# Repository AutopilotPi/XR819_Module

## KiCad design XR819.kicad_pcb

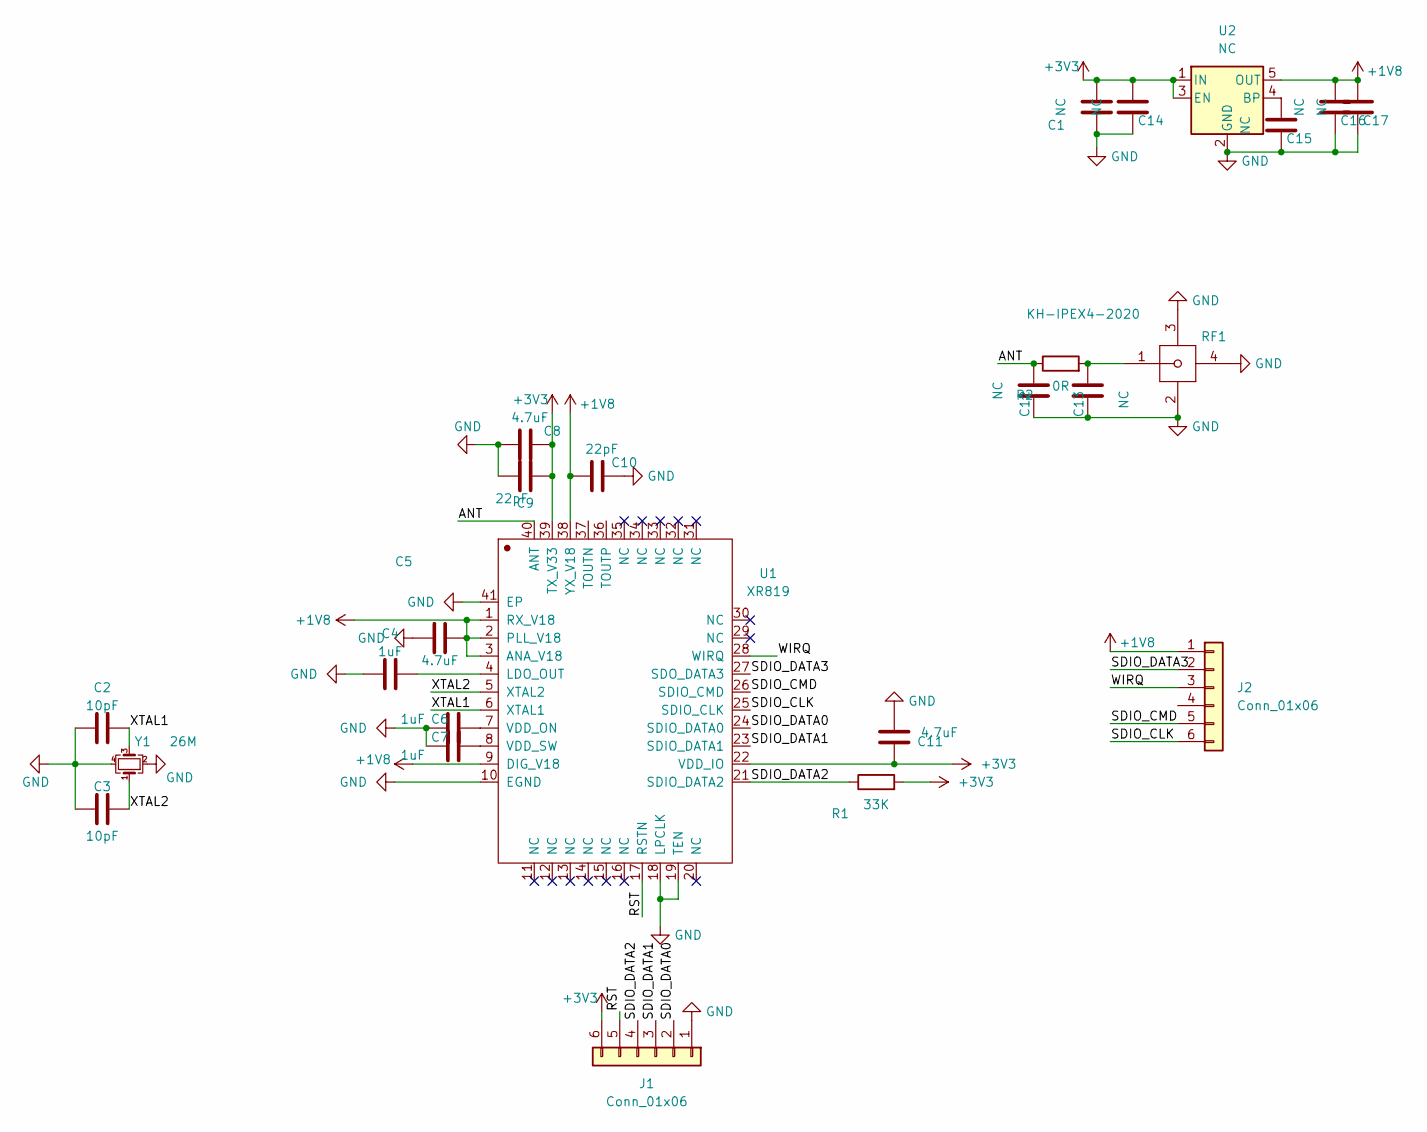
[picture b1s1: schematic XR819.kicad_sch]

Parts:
C1, C12, C13, C14, C15, C16, C17: NC; C_0402_1005Metric
C2, C3: 10pF; C_0402_1005Metric
C4, C6, C7: 1uF; C_0402_1005Metric
C5, C8, C11: 4.7uF; C_0402_1005Metric
C9, C10: 22pF; C_0402_1005Metric
J1, J2: Conn_01x06; PinHeader_1x06_P2.00mm_Vertical
R1: 33K; R_0402_1005Metric
R2: 0R; R_0402_1005Metric
RF1: KH-IPEX4-2020; IPEX4-SMD_4P-L1.8-W1.7-LS2.0-L_KH-IPEX4-2020
U1: XR819; QFN-40_L5.0-W5.0-P0.40-TL-EP3.4
U2: NC; SOT-23-5
Y1: 26M; Crystal_SMD_EuroQuartz_MT-4Pin_3.2x2.5mm

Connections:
+1V8: C5.1, C10.2, C16.2, C17.2, J2.1, U1.1 (RX_V18), U1.2 (PLL_V18), U1.3 (ANA_V18), U1.9 (DIG_V18), U1.38 (YX_V18), U2.5 (OUT)
+3V3: C1.2, C8.1, C9.1, C11.1, C14.2, J1.6, R1.2, U1.22 (VDD_IO), U1.39 (TX_V33), U2.1 (IN), U2.3 (EN)
/ANT: C12.2, R2.1, U1.40 (ANT)
/RST: J1.5, U1.17 (RSTN)
/SDIO_CLK: J2.6, U1.25 (SDIO_CLK)
/SDIO_CMD: J2.5, U1.26 (SDIO_CMD)
/SDIO_DATA0: J1.2, U1.24 (SDIO_DATA0)
/SDIO_DATA1: J1.3, U1.23 (SDIO_DATA1)
/SDIO_DATA2: J1.4, R1.1, U1.21 (SDIO_DATA2)
/SDIO_DATA3: J2.2, U1.27 (SDO_DATA3)
/WIRQ: J2.3, U1.28 (WIRQ)
/XTAL1: C2.2, U1.6 (XTAL1), Y1.3
/XTAL2: C3.2, U1.5 (XTAL2), Y1.1
GND: C1.1, C2.1, C3.1, C4.1, C5.2, C6.1, C7.1, C8.2, C9.2, C10.1, C11.2, C12.1, C13.1, C14.1, C15.1, C16.1, C17.1, J1.1, RF1.2, RF1.3, RF1.4, U1.10 (EGND), U1.18 (LPCLK), U1.19 (TEN), U1.41 (EP), U2.2 (GND), Y1.2, Y1.4
unnamed: C4.2, U1.4 (LDO_OUT)
unnamed: C6.2, U1.7 (VDD_ON)
unnamed: C7.2, U1.8 (VDD_SW)
unnamed: C13.2, R2.2, RF1.1
unnamed: C15.2, U2.4 (BP)

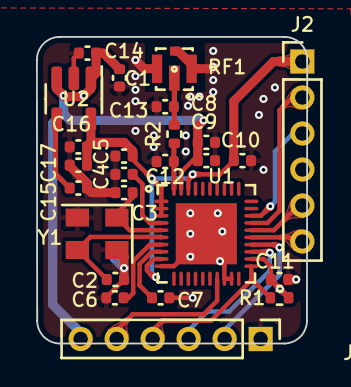
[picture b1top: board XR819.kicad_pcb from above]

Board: 4 copper layers, 15.0 x 17.0 mm, 25 parts (0 on the bottom side), 19 nets.

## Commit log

2022-07-02 init
2022-07-13 add comment on osc
2022-07-15 add sch pdf
